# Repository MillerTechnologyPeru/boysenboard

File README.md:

# BoysenBoard
Linux capable single board computer using the F1C200s in an Arduino form-factor.

## Build
The BoysenBoard supports booting from the on-board 16MB of SPI flash or from a 
Micro-SD card. The board will first try to boot from the SD card. If that 
fails, it will try the SPI flash. Otherwise it will enter FEL bootloader mode. 

### Setting up the Buildroot Environment
Clone this repo:
```
git clone https://github.com/mclewell/boysenboard
git submodule update --init
```
Change to the Buildroot directory:
```
cd boysenboard/software/buildroot
```

### Building the SPI Flash Image
We will be doing an out-of-tree build. Make an directory for the output:
```
mkdir output-spi
cd output-spi
```
Set-up the build:
```
make -C ../ O=$(pwd) BR2_EXTERNAL=$PWD/../../ boysenboard_spi_defconfig
```
Start the build (on my Ryzen 3900X this took about 7mins):
```
make
```
Once complete, the resulting flash image will be at:
```
images/flash.bin
```
To flash images into the SPI flash, the board must be in FEL mode. If the SPI 
flash is blank, the board will automatically enter FEL mode. If a valid boot 
image already exists in the flash, the board can be placed into FEL mode using
a special SD-Card image.
```
wget https://github.com/linux-sunxi/sunxi-tools/raw/master/bin/fel-sdboot.sunxi
dd if=fel-sdboot.sunxi of=/dev/sdX bs=1024 seek=8
```
Note: ensure the board is fully powered down. Sometimes external USB-UART cables
will back-power the board.

Insert the FEL SD-Card and connect the USB cable. FEL mode can be verified by 
using ```lsusb```:
```
Bus 005 Device 010: ID 1f3a:efe8 Allwinner Technology sunxi SoC OTG connector in FEL/flashing mode
```
Start the flashing process with:
```
sudo host/bin/sunxi-fel -p spiflash-write 0 images/flash.bin
```
This process will take about 3mins. Once complete, remove the USB cable and 
SD-Card. Connect to the serial console on UART0 to see console output messages.

The first boot after flashing a new image will take a while as U-Boot sets up 
the UBIFS. Subsequent boots will be much fast. You will see the following 
messages from U-Boot while this occurs:
```
...
SF: Detected w25q128 with page size 256 Bytes, erase size 64 KiB, total 16 MiB
ubi0: attaching mtd2
ubi0: scanning is finished
ubi0: attached mtd2 (name "rootubi", size 15 MiB)
ubi0: PEB size: 65536 bytes (64 KiB), LEB size: 65408 bytes
ubi0: min./max. I/O unit sizes: 1/256, sub-page size 1
ubi0: VID header offset: 64 (aligned 64), data offset: 128
ubi0: good PEBs: 252, bad PEBs: 0, corrupted PEBs: 0
ubi0: user volume: 5, internal volumes: 1, max. volumes count: 128
ubi0: max/mean erase counter: 0/0, WL threshold: 4096, image sequence number: 1562368489
ubi0: available PEBs: 12, total reserved PEBs: 240, PEBs reserved for bad PEB handling: 0
...
```

Once booted, the login information is:
```
User: root
Password: [none]
```
The SPI flash image also sets the board up as a USB Gadget presenting the host
computer with a serial COM port device and USB mass storage. The serial port
typically enumerates as /dev/ttyACM0. 

### Building the SD Card Image
Like the SPI image,  we will be doing an out-of-tree build. Make an directory 
for the output:
```
mkdir output-sd
cd output-sd
```
Set-up the build:
```
make -C ../ O=$(pwd) BR2_EXTERNAL=$PWD/../../ boysenboard_sd_defconfig
```
Start the build (on my Ryzen 3900X this took about 7mins):
```
make
```
Once complete, the resulting SD-Card image will be at:
```
images/sdcard.img
```
Write the image to an SD-Card:
```
sudo dd if=image/sdcard.img of=/dev/sdX bs=1M status=progress && sync
```
Note: the SD-Card image does not enable the USB Gadget feature.

# Acknowledgements
This project is derived from [George Hillard's busiesscard-linux](https://github.com/thirtythreeforty/businesscard-linux)
project. 

Also thanks to [Icenowy](https://github.com/Icenowy) for their work getting U-Boot and Linux running
on the F1C100s and F1C200s processors.

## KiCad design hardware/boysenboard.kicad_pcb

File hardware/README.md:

# Known Issues
- Silk swapped for R17 and C19
- Alignment holes for J1 are too small
- Add paste aperatures for SD-Card socket (J5)
- Add paste aperatures for GND hole pads on USB connector (J1)
- Add buffers on UART0 (my external tools are back-powering through the F1C200s 
ESD diodes)
- Remove UART0 RX/TX from LEDs and replace with other GPIO (LEDs are always on 
and 115200 baud is too fast for any meaningful blinking)
- Button or jumper to enter FEL Mode by holding SPI0_CS low.

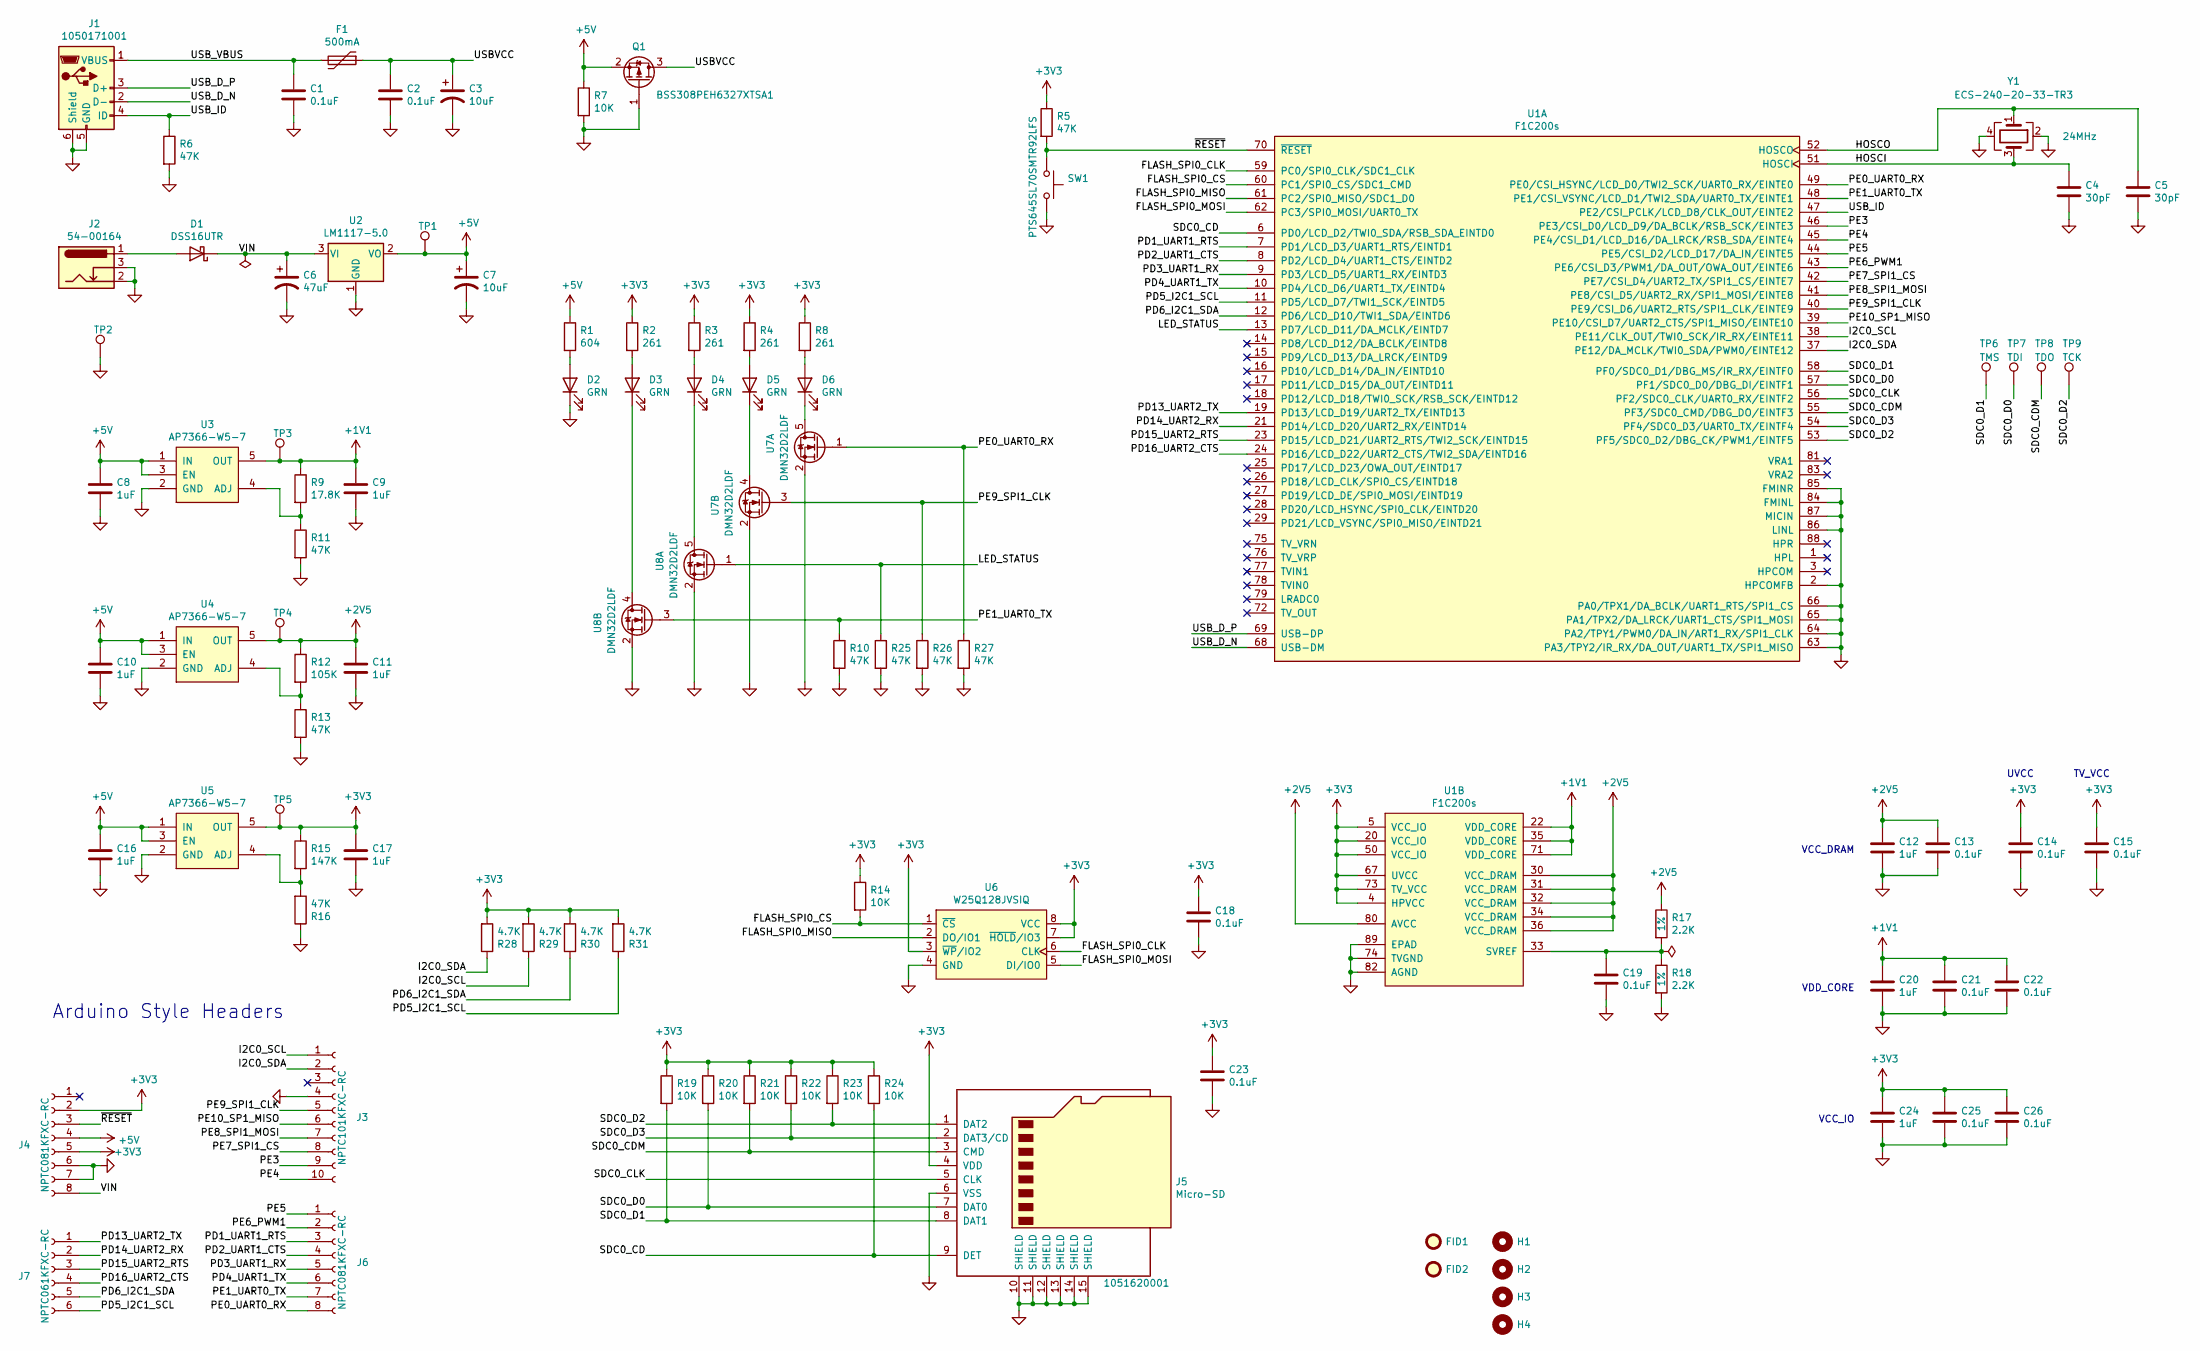
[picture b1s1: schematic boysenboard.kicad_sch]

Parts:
C1, C2, C13, C14, C15, C18, C19, C21, C22, C23, C25, C26: 0.1uF; C_0603_1608Metric; PartNumber CL10B104KB8NNNL
C3, C7: 10uF; CP_EIA-3216-18_Kemet-A; PartNumber TAJA106K016SNJ
C4, C5: 30pF; C_0603_1608Metric; PartNumber CC0603JRNPO9BN300
C6: 47uF; CP_Elec_6.3x5.8; PartNumber 875105344006
C8, C9, C10, C11, C12, C16, C17, C20, C24: 1uF; C_0603_1608Metric; PartNumber CL10B105KA8NFNC
D1: DSS16UTR; D_SOD-123F; PartNumber DSS16UTR
D2, D3, D4, D5, D6: GRN; LED_1206_3216Metric_Castellated; PartNumber 150120VS75000
F1: 500mA; Fuse_1206_3216Metric_Castellated; PartNumber PTS120615V050
FID1, FID2: Fiducial; Fiducial_1.5mm_Mask3mm
H1, H2, H3, H4: MountingHole; mounting_hole_125mil
J1: 1050171001; USB_Micro-B_Molex-105017-0001; PartNumber 1050171001
J2: 54-00164; barrel_jack_2.1mm; PartNumber 54-00164
J3: NPTC101KFXC-RC; PinSocket_1x10_P2.54mm_Vertical_SMD_Pin1Right; PartNumber NPTC101KFXC-RC
J4, J6: NPTC081KFXC-RC; PinSocket_1x08_P2.54mm_Vertical_SMD_Pin1Right; PartNumber NPTC081KFXC-RC
J5: Micro-SD; micro-sd; PartNumber 1051620001
J7: NPTC061KFXC-RC; PinSocket_1x06_P2.54mm_Vertical_SMD_Pin1Right; PartNumber NPTC061KFXC-RC
Q1: BSS308PEH6327XTSA1; SOT-23; PartNumber BSS308PEH6327XTSA1
R1: 604; R_0603_1608Metric; PartNumber RMCF0603FT604R
R2, R3, R4, R8: 261; R_0603_1608Metric; PartNumber RMCF0603FT261R
R5, R6, R10, R11, R13, R16, R25, R26, R27: 47K; R_0603_1608Metric; PartNumber RMCF0603FT47K0
R7, R14, R19, R20, R21, R22, R23, R24: 10K; R_0603_1608Metric; PartNumber RMCF0603FT10K0
R9: 17.8K; R_0603_1608Metric; PartNumber RMCF0603FG17K8
R12: 105K; R_0603_1608Metric; PartNumber RMCF0603FT105K
R15: 147K; R_0603_1608Metric; PartNumber RMCF0603FT147K
R17, R18: 2.2K; R_0603_1608Metric; Tolerance 1%; PartNumber RMCF0603FT2K20
R28, R29, R30, R31: 4.7K; R_0603_1608Metric; PartNumber RMCF0603FT4K70
SW1: PTS645SL70SMTR92LFS; switch_tactile_6x6mm_smt; PartNumber PTS645SL70SMTR92LFS
TP1, TP2, TP3, TP4, TP5: TestPoint; test_point_RCSCTE
TP6: TMS; TestPoint_Pad_D1.0mm
TP7: TDI; TestPoint_Pad_D1.0mm
TP8: TDO; TestPoint_Pad_D1.0mm
TP9: TCK; TestPoint_Pad_D1.0mm
U1: F1C200s; QFN-88; PartNumber F1C200s
U2: LM1117-5.0; SOT-223-3_TabPin2; PartNumber LM1117MPX-5.0
U3, U4, U5: AP7366-W5-7; SOT-23-6; PartNumber AP7366-W5-7
U6: W25Q128JVSIQ; SO-8_5.3x6.2mm_P1.27mm; PartNumber W25Q128JVSIQ
U7, U8: DMN32D2LDF; SOT-353_SC-70-5; PartNumber DMN32D2LDF-7
Y1: 24MHz; Crystal_SMD_Abracon_ABM8G-4Pin_3.2x2.5mm; PartNumber ECS-240-20-33-TR3

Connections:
+1V1: C9.1, C20.1, C21.1, C22.1, R9.1, TP3.1, U1.22 (VDD_CORE), U1.35 (VDD_CORE), U1.71 (VDD_CORE), U3.5 (OUT)
+2V5: C11.1, C12.1, C13.1, R12.1, R17.1, TP4.1, U1.30 (VCC_DRAM), U1.31 (VCC_DRAM), U1.32 (VCC_DRAM), U1.34 (VCC_DRAM), U1.36 (VCC_DRAM), U1.80 (AVCC), U4.5 (OUT)
+3V3: C14.1, C15.1, C17.1, C18.1, C23.1, C24.1, C25.1, C26.1, J4.2, J4.5, J5.4 (VDD), R2.1, R3.1, R4.1, R5.1, R8.1, R14.1, R15.1, R19.1, R20.1, R21.1, R22.1, R23.1, R24.1, R28.2, R29.2, R30.2, R31.2, TP5.1, U1.4 (HPVCC), U1.5 (VCC_IO), U1.20 (VCC_IO), U1.50 (VCC_IO), U1.67 (UVCC), U1.73 (TV_VCC), U5.5 (OUT), U6.3 (~WP/IO2), U6.7 (~HOLD/IO3), U6.8 (VCC)
+5V: C7.1, C8.1, C10.1, C16.1, J4.4, Q1.2 (S), R1.1, R7.1, TP1.1, U2.2 (VO), U3.1 (IN), U3.3 (EN), U4.1 (IN), U4.3 (EN), U5.1 (IN), U5.3 (EN)
/FLASH_SPI0_CLK: U1.59 (PC0/SPI0_CLK/SDC1_CLK), U6.6 (CLK)
/FLASH_SPI0_CS: R14.2, U1.60 (PC1/SPI0_CS/SDC1_CMD), U6.1 (~CS)
/FLASH_SPI0_MISO: U1.61 (PC2/SPI0_MISO/SDC1_D0), U6.2 (DO/IO1)
/FLASH_SPI0_MOSI: U1.62 (PC3/SPI0_MOSI/UART0_TX), U6.5 (DI/IO0)
/HOSCI: C4.1, U1.51 (HOSCI), Y1.3
/HOSCO: C5.1, U1.52 (HOSCO), Y1.1
/I2C0_SCL: J3.1, R29.1, U1.38 (PE11/CLK_OUT/TWI0_SCK/IR_RX/EINTE11)
/I2C0_SDA: J3.2, R28.1, U1.37 (PE12/DA_MCLK/TWI0_SDA/PWM0/EINTE12)
/LED_STATUS: R25.1, U1.13 (PD7/LCD_D11/DA_MCLK/EINTD7), U8.1 (G1)
/PD1_UART1_RTS: J6.3, U1.7 (PD1/LCD_D3/UART1_RTS/EINTD1)
/PD2_UART1_CTS: J6.4, U1.8 (PD2/LCD_D4/UART1_CTS/EINTD2)
/PD3_UART1_RX: J6.5, U1.9 (PD3/LCD_D5/UART1_RX/EINTD3)
/PD4_UART1_TX: J6.6, U1.10 (PD4/LCD_D6/UART1_TX/EINTD4)
/PD5_I2C1_SCL: J7.6, R31.1, U1.11 (PD5/LCD_D7/TWI1_SCK/EINTD5)
/PD6_I2C1_SDA: J7.5, R30.1, U1.12 (PD6/LCD_D10/TWI1_SDA/EINTD6)
/PD13_UART2_TX: J7.1, U1.19 (PD13/LCD_D19/UART2_TX/EINTD13)
/PD14_UART2_RX: J7.2, U1.21 (PD14/LCD_D20/UART2_RX/EINTD14)
/PD15_UART2_RTS: J7.3, U1.23 (PD15/LCD_D21/UART2_RTS/TWI2_SCK/EINTD15)
/PD16_UART2_CTS: J7.4, U1.24 (PD16/LCD_D22/UART2_CTS/TWI2_SDA/EINTD16)
/PE0_UART0_RX: J6.8, R27.1, U1.49 (PE0/CSI_HSYNC/LCD_D0/TWI2_SCK/UART0_RX/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), U7.1 (G1)
/PE1_UART0_TX: J6.7, R10.1, U1.48 (PE1/CSI_VSYNC/LCD_D1/TWI2_SDA/UART0_TX/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), U8.3 (G2)
/PE3: J3.9, U1.46 (PE3/CSI_D0/LCD_D9/DA_BCLK/RSB_SCK/EINTE3)
/PE4: J3.10, U1.45 (PE4/CSI_D1/LCD_D16/DA_LRCK/RSB_SDA/EINT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)
/PE5: J6.1, U1.44 (PE5/CSI_D2/LCD_D17/DA_IN/EINTE5)
/PE6_PWM1: J6.2, U1.43 (PE6/CSI_D3/PWM1/DA_OUT/OWA_OUT/EINTE6)
/PE7_SPI1_CS: J3.8, U1.42 (PE7/CSI_D4/UART2_TX/SPI1_CS/EINTE7)
/PE8_SPI1_MOSI: J3.7, U1.41 (PE8/CSI_D5/UART2_RX/SPI1_MOSI/EINTE8)
/PE9_SPI1_CLK: J3.5, R26.1, U1.40 (PE9/CSI_D6/UART2_RTS/SPI1_CLK/EINTE9), U7.3 (G2)
/PE10_SP1_MISO: J3.6, U1.39 (PE10/CSI_D7/UART2_CTS/SPI1_MISO/EINTE10)
/SDC0_CD: J5.9 (DET), R24.2, U1.6 (PD0/LCD_D2/TWI0_SDA/RSB_SDA_EINTD0)
/SDC0_CDM: J5.3 (CMD), R21.2, TP8.1, U1.55 (PF3/SDC0_CMD/DBG_DO/EINTF3)
/SDC0_CLK: J5.5 (CLK), U1.56 (PF2/SDC0_CLK/UART0_RX/EINTF2)
/SDC0_D0: J5.7 (DAT0), R20.2, TP7.1, U1.57 (PF1/SDC0_D0/DBG_DI/EINTF1)
/SDC0_D1: J5.8 (DAT1), R19.2, TP6.1, U1.58 (PF0/SDC0_D1/DBG_MS/IR_RX/EINTF0)
/SDC0_D2: J5.1 (DAT2), R23.2, TP9.1, U1.53 (PF5/SDC0_D2/DBG_CK/PWM1/EINTF5)
/SDC0_D3: J5.2 (DAT3/CD), R22.2, U1.54 (PF4/SDC0_D3/UART0_TX/EINTF4)
/USBVCC: C2.1, C3.1, F1.1, Q1.3 (D)
/USB_D_N: J1.2 (D-), U1.68 (USB-DM)
/USB_D_P: J1.3 (D+), U1.69 (USB-DP)
/USB_ID: J1.4 (ID), R6.1, U1.47 (PE2/CSI_PCLK/LCD_D8/CLK_OUT/EINTE2)
/USB_VBUS: C1.1, F1.2, J1.1 (VBUS)
/VIN: C6.1, D1.1 (K), J4.8, U2.3 (VI)
/~RESET: J4.3, R5.2, SW1.1, U1.70 (~RESET)
GND: C1.2, C2.2, C3.2, C4.2, C5.2, C6.2, C7.2, C8.2, C9.2, C10.2, C11.2, C12.2, C13.2, C14.2, C15.2, C16.2, C17.2, C18.2, C19.2, C20.2, C21.2, C22.2, C23.2, C24.2, C25.2, C26.2, D2.1 (K), J1.5 (GND), J1.6 (Shield), J2.2, J2.3, J3.4, J4.6, J4.7, J5.6 (VSS), J5.10 (SHIELD), J5.11 (SHIELD), J5.12 (SHIELD), J5.13 (SHIELD), J5.14 (SHIELD), J5.15 (SHIELD), Q1.1 (G), R6.2, R7.2, R10.2, R11.2, R13.2, R16.1, R18.2, R25.2, R26.2, R27.2, SW1.2, TP2.1, U1.2 (HPCOMFB), U1.63 (PA3/TPY2/IR_RX/DA_OUT/UART1_TX/SPI1_MISO), U1.64 (PA2/TPY1/PWM0/DA_IN/ART1_RX/SPI1_CLK), U1.65 (PA1/TPX2/DA_LRCK/UART1_CTS/SPI1_MOSI), U1.66 (PA0/TPX1/DA_BCLK/UART1_RTS/SPI1_CS), U1.74 (TVGND), U1.82 (AGND), U1.84 (FMINL), U1.85 (FMINR), U1.86 (LINL), U1.87 (MICIN), U1.89 (EPAD), U2.1 (GND), U3.2 (GND), U4.2 (GND), U5.2 (GND), U6.4 (GND), U7.2 (S), U8.2 (S), Y1.2, Y1.4
unnamed: C19.1, R17.2, R18.1, U1.33 (SVREF)
unnamed: D1.2 (A), J2.1
unnamed: D2.2 (A), R1.2
unnamed: D3.1 (K), U8.4 (D2)
unnamed: D3.2 (A), R2.2
unnamed: D4.1 (K), U8.5 (D1)
unnamed: D4.2 (A), R3.2
unnamed: D5.1 (K), U7.4 (D2)
unnamed: D5.2 (A), R4.2
unnamed: D6.1 (K), U7.5 (D1)
unnamed: D6.2 (A), R8.2
unnamed: R9.2, R11.1, U3.4 (ADJ)
unnamed: R12.2, R13.1, U4.4 (ADJ)
unnamed: R15.2, R16.2, U5.4 (ADJ)

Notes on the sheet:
UVCC
TV_VCC
VDD_CORE
VCC_IO
Arduino Style Headers
VCC_DRAM

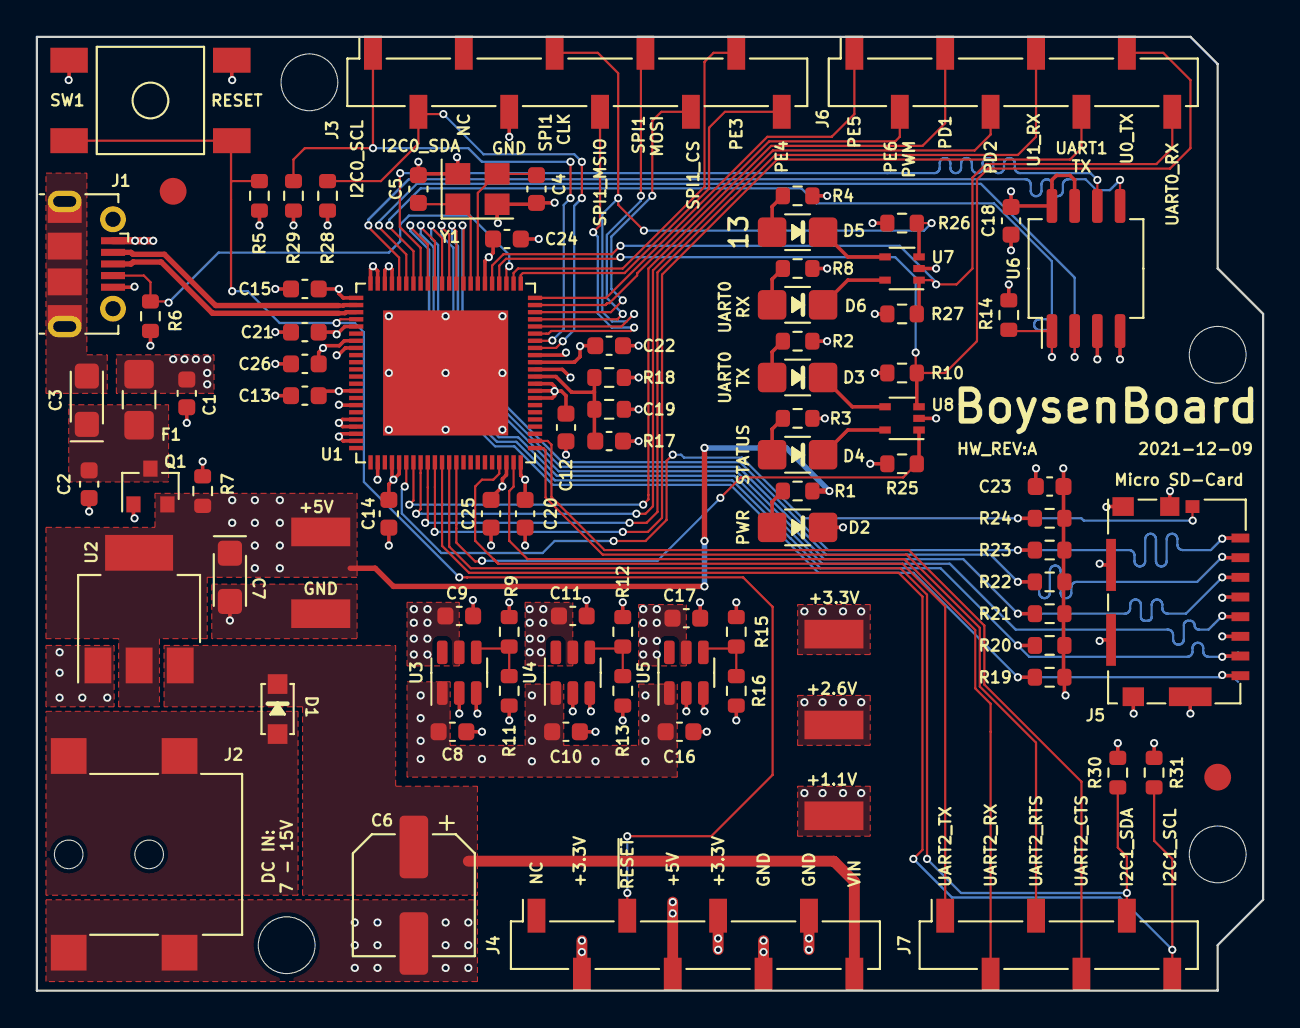
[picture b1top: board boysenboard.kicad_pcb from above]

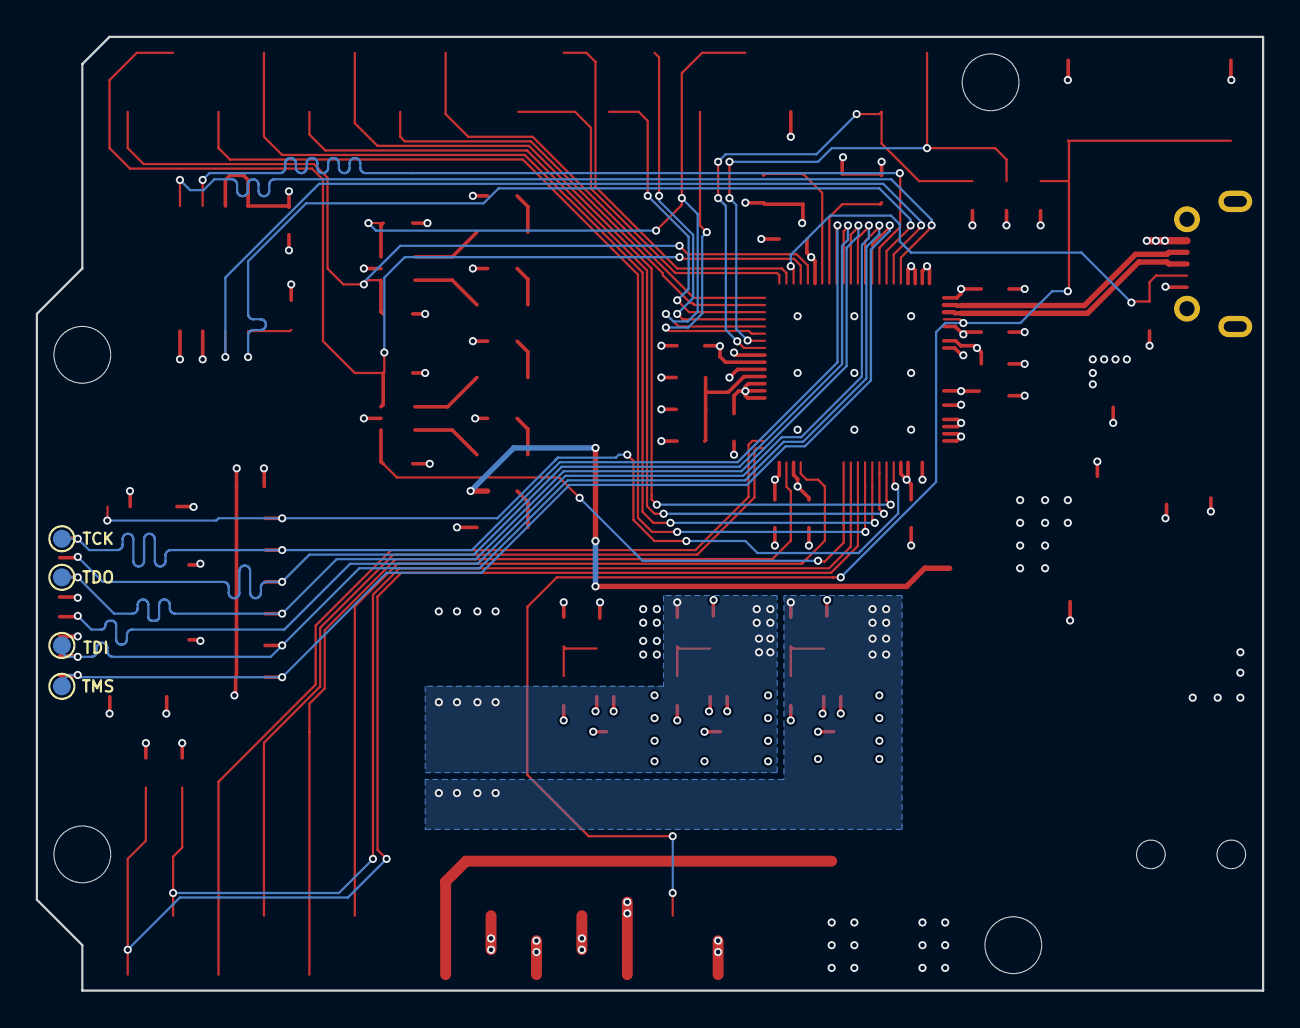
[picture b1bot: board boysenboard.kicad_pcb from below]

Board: 4 copper layers, 68.6 x 53.3 mm, 97 parts (4 on the bottom side), 62 nets.

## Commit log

2022-01-02 Fixed footprint references and kicad 5->6 models
2022-01-02 Fixed PCB DRC violations caused by Kicad 5->6 conversion
2022-01-02 Fixed buildroot version
2022-01-06 Added hardwware known issues
2022-02-02 Added acknowledgements to readme
2022-02-02 Readme formatting fixes.

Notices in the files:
hardware/boysenboard.kicad_sch:
License: GPL3
